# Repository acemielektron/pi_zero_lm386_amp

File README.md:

# LM386 based audio amplifier for raspberry pi zero

This is a lm386 based amp designed for rpi0. As rpi0 does not have an audio output jack like the rpi b or rpi a another option is needed. There are three options: last two being an usb sound card and i2s sound board which are both comparatively expensive and add more bulk to your project. First choice is gpio sound output. But gpio sound output is a it problematic that is: it is very noisy. To suppress noise a band pass filter consisting a low pass filter and a high pass filter is used. Filtered output is weak so an amplifier is necessary. Amplifier of choice is PAM8403 based stereo amp board which is both cheap and small. 

Although PAM8403 is likely most used amp in diy projects as i already had lm386 ic i decided to use it. So i designed a compact pcb in eagle based on lm386 for fitting in an diy handheld gaming console housing. I used http://www.circuitbasics.com/build-a-great-sounding-audio-amplifier-with-bass-boost-from-the-lm386/ and LM386 datasheet as references. If you decide to use this project remember while PAM8403 is a class D amplifier LM386 is a class B amplifier. So it is likely PAM8403 is more energy efficient.

I have already mentioned the noise and despite band pass filter there is unbearable noise to hear acceptable sounds from rpi0 you need to change config.txt in BOOT partition as follows:

<i>
#pwm-audio on gpio 18 and 13<br>
##dtoverlay=pwm-2chan,pin=18,func=2,pin2=13,func2=4<br>
dtoverlay=pwm,pin=13,func=4<br>
disable_audio_dither=1<br>
audio_pwm_mode=1<br>
</i>

<br>Settings <i>"audio_pwm_mode=1"</i> and <i>"disable_audio_dither=1"</i> for suppressing noise. Commented out configuration is for two channel output which is not necessary for mono LM386 amp.

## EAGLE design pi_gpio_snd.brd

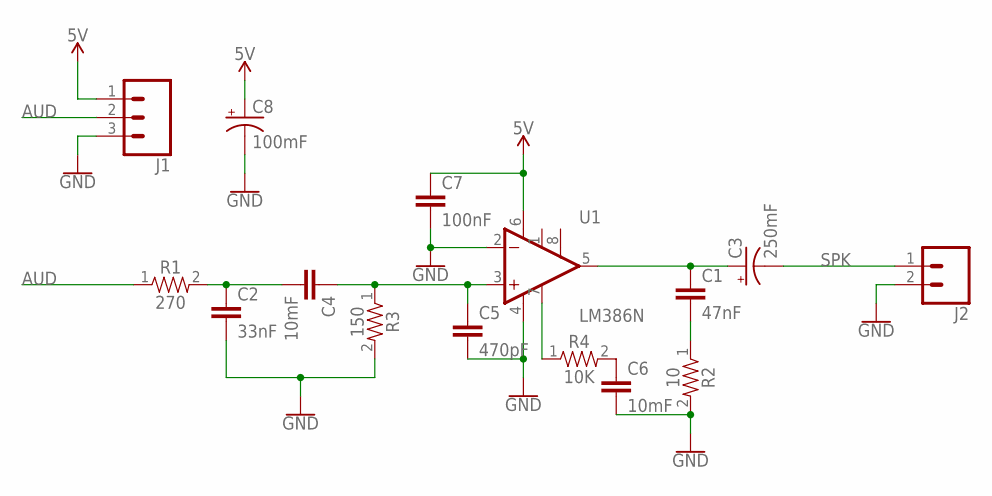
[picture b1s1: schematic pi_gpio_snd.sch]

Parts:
C1: 47nF; 1206
C2: 33nF; 1206
C3: 250mF; CPOL-RADIAL-5MM-10MM
C4, C6: 10mF; 0805
C5: 470pF; 1206
C7: 100nF; 0805
C8: 100mF; CPOL-RADIAL-5MM-10MM
J1: CONN_03; 1X03
J2: CONN_02; 1X02
R1: 270; 1206
R2: 10; 1206
R3: 150; 1206
R4: 10K; 1206
U1: LM386N; DIP08

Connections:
5V: C7.1, C8.+, J1.1, U1.6 (V+)
AUD: J1.2, R1.1
GND: C2.2, C5.2, C6.2, C7.2, C8.-, J1.3, J2.2, R2.2, R3.2, U1.2 (-IN), U1.4 (V-)
unnamed: C1.1, C3.+, U1.5 (OUT)
unnamed: C2.1, C4.2, R1.2
unnamed: C4.1, C5.1, R3.1, U1.3 (+IN)
unnamed: C1.2, R2.1
unnamed: R4.1, U1.7 (BP)
unnamed: C6.1, R4.2
SPK: C3.-, J2.1

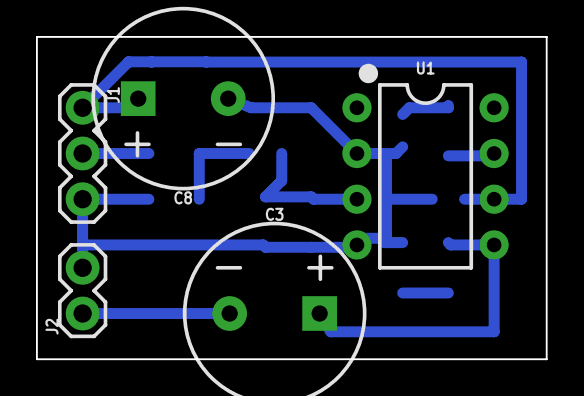
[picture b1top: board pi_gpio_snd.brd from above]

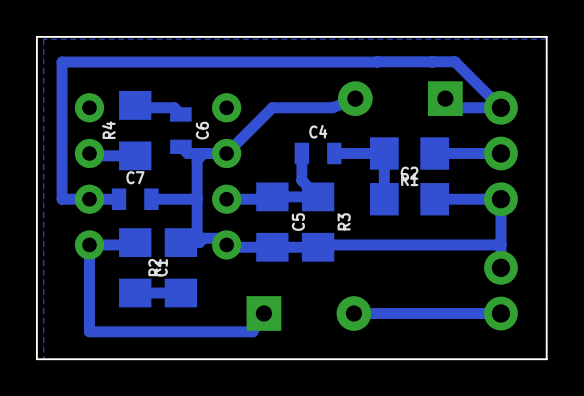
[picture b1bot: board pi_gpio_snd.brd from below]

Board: 2 copper layers, 28.3 x 17.9 mm, 15 parts (10 on the bottom side), 10 nets.

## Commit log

2019-07-24 Cleanup

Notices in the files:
parts and their libraries:
SparkFun-Capacitors: Licensing: Creative Commons ShareAlike 4.0 International - https://creativecommons.org/licenses/by-sa/4.0
